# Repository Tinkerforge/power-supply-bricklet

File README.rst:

Power Supply Bricklet
=====================

**This Bricklet is currently in development.**

This repository contains the firmware source code and the hardware design
files. The documentation generator configs can be found at
https://github.com/Tinkerforge/generators

Repository Content
------------------

software/:
 * examples/: Examples for all supported languages
 * build/: Compiled files
 * src/: Source code of firmware
 * Makefile: Makefile to build project

hardware/:
 * Contains KiCad project files and additionally schematics as PDF

datasheets/:
 * Contains datasheets for sensors and complex ICs that are used

Hardware
--------

The hardware is designed with the open source EDA Suite KiCad
(http://www.kicad.org). Before you are able to open the files,
you have to install the Tinkerforge kicad-libraries
(https://github.com/Tinkerforge/kicad-libraries). You can either clone
them directly in hardware/ or clone them in a separate folder and
symlink them into hardware/
(ln -s kicad_path/kicad-libraries project_path/hardware). After that you
can open the .pro file in hardware/ with KiCad and from there view and
modify the schematics and the PCB layout.

Software
--------

If you want to do your own Brick/Bricklet firmware development we highly
recommend that you use our build environment setup script and read the
tutorial (https://www.tinkerforge.com/en/doc/Tutorials/Tutorial_Build_Environment/Tutorial.html).

To compile the C code we recommend you to install the newest GNU Arm Embedded
Toolchain (https://launchpad.net/gcc-arm-embedded/+download).
You also need to install bricklib2 (https://github.com/Tinkerforge/bricklib2).

You can either clone it directly in software/src/ or clone it in a
separate folder and symlink it into software/src/
(ln -s bricklib_path/bricklib2 project_path/software/src/). Finally make sure to
have CMake installed (http://www.cmake.org/cmake/resources/software.html).

After that you can build the firmware by invoking make in software/.
The firmware (.zbin) can then be found in software/build/ and uploaded
with brickv (click button "Flashing" on start screen).

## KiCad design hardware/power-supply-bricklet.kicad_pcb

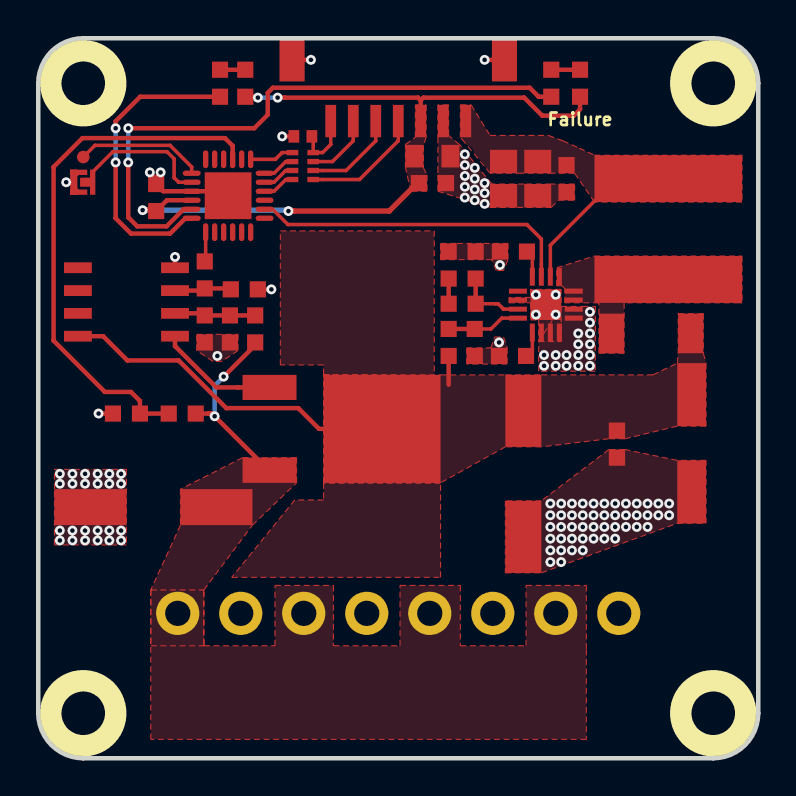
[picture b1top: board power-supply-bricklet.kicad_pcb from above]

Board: 2 copper layers, 40.0 x 40.0 mm, 44 parts (0 on the bottom side), 31 nets.

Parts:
C1: 220pF; C0402F
C2: 10uF; C0805
C3, C4, C8, C9: 100nF; C0603F
C5: 1uF; C0603F
C6, C7: 10uF; C0805E
C11: 27nF; C0603F
C12: 2,2nF; C0603F
C13: 120nF; C0603F
C14: 10uF 50V; ELKO_63
C15: 680nF 50V; C0603F
C16, C17: 220uF 50V; ELKO_83
D1: blue; D0603F
D2: red; D0603F
D3: PMEG4050; SOD-128
L1: SRN8040-100M/10uH; SRN8040
P1: CON-SENSOR; CON-SENSOR2
P2: Debug; DEBUG_PAD
P3: Boot; SolderJumper
P4: Output; OQ_8P
Q1: FQD10N20C; TO-252-3L
R1, R2, R5, R10: 1k; R0603F
R3: 470k; R0603F
R4: 68k; R0603F
R7: 60; R0603F
R8: 2k; R0603F
R9, R14: 10k; R0603F
R13: 220k; R0603F
RP1: 82; 4X0402
U1: XMC1100; QFN24-4x4mm-0.5mm
U2: OPA1678; SOIC8
U3, U4, U5, U6: DRILL; DRILL_NP
U7: TPS55340; S-PWQFN-N16

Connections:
5V: C6.1, C7.1, C8.1, L1.1, P1.1, U7.2
+VSW: C14.1, C15.1, C16.1, D3.2, Q1.D, R13.1, U2.8
Enable: U1.20, U7.3
FB0: R9.2, R10.1, U1.3
GND: C1.2, C2.2, C3.2, C4.2, C5.2, C6.2, C7.2, C8.2, C9.2, C11.2, C12.2, C13.2, C14.2, C15.2, C16.2, C17.2, P1.2, P1.EP, P3.1, P4.2, P4.4, P4.6, P4.8, R4.2, R7.2, R10.2, R14.2, U1.9, U1.EXP, U2.4, U7.6, U7.10, U7.11, U7.12, U7.13, U7.14, U7.17
unnamed: C1.1, P1.7, RP1.4
unnamed: C9.1, R3.2, R4.1, U2.2
unnamed: C11.1, U7.4
unnamed: C12.1, R8.2, U7.7
unnamed: C13.1, R8.1
unnamed: D1.2, R2.2
unnamed: D2.2, R5.2
unnamed: D3.1, L1.2, U7.1, U7.15, U7.16
unnamed: P1.4, RP1.1
unnamed: P1.5, RP1.2
unnamed: P1.6, RP1.3
unnamed: P2.1, U1.7
unnamed: P3.2, U1.8
unnamed: Q1.G, U2.1
unnamed: R1.1, U1.13
unnamed: R2.1, U1.12
unnamed: R5.1, U1.11
unnamed: R7.1, U7.9
unnamed: R13.2, R14.1, U7.8
PWM0: C5.1, R1.2, U2.3
S-CLK: RP1.7, U1.23
S-CS: RP1.8, U1.22
S-MISO: RP1.5, U1.1
S-MOSI: RP1.6, U1.24
VCC: C2.1, C3.1, C4.1, D1.1, D2.1, P1.3, U1.10
Vo0: C17.1, P4.1, P4.3, P4.5, P4.7, Q1.S, R3.1, R9.1

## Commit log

2018-11-19 add basic files
2018-11-20 add design files of first prototype
2019-02-06 add fiducials, ordered version
2019-04-11 added datasheets, new schematics design
2019-04-15 new design
2019-04-16 final prototype design
2019-05-13 fix file name
2019-05-16 Add .gitignore
2021-10-25 Update KiCad link
    https://www.kicad.org/blog/2021/10/Avoid-links-to-former-kicad-domain/

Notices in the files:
hardware/power-supply-bricklet.kicad_pcb:
Licensed under CERN OHL v.1.1
Copyright (©) 2018, B.Nordmeyer
Copyright Tinkerforge GmbH 2018.
This documentation describes Open Hardware and is licensed under the
CERN OHL v. 1.1.
